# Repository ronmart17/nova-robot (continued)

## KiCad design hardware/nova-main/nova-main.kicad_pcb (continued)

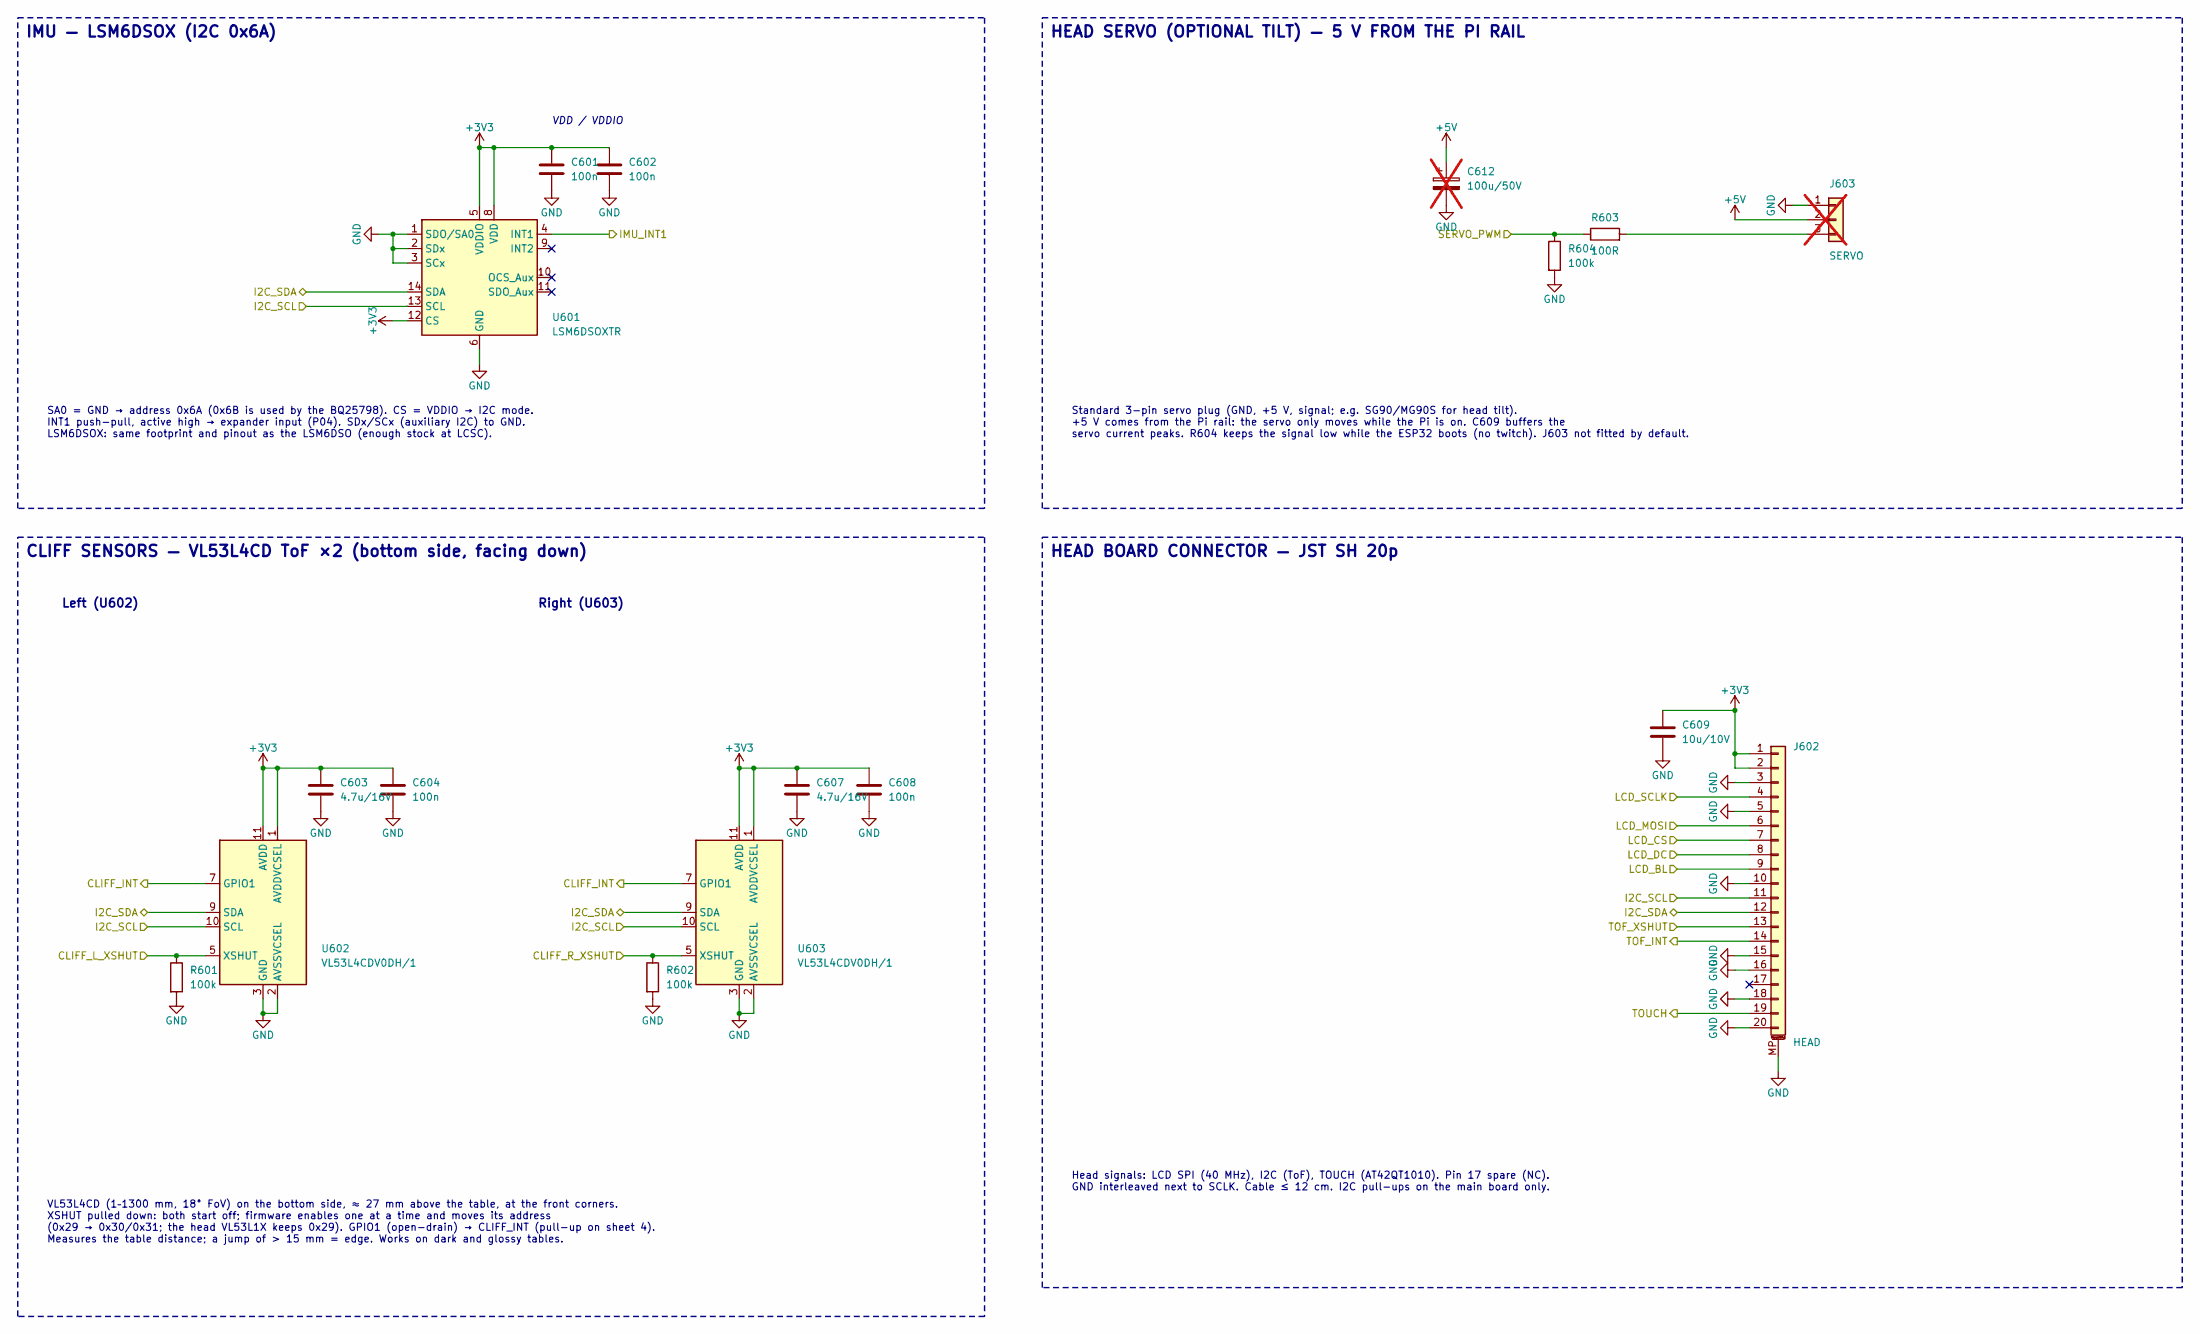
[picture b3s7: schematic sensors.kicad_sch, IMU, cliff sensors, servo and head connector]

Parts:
C601, C602, C604, C608: 100n; C_0402_1005Metric; Voltage 50V; MPN CL05B104KB54PNC; LCSC C307331
C603, C607: 4.7u/16V; C_0603_1608Metric; Voltage 16V; MPN CL10A475KO8NNNC; LCSC C19666
C609: 10u/10V; C_0603_1608Metric; Voltage 10V; MPN CC0603KRX5R6BB106; LCSC C326057
C612: 100u/50V; CP_Elec_6.3x7.7; Voltage 50V; MPN EEE-FTH101XAP; LCSC C165974; not fitted
J602: HEAD; JST_SH_SM20B-SRSS-TB_1x20-1MP_P1.00mm_Horizontal; MPN SM20B-SRSS-TB(LF)(SN); LCSC C160415
J603: SERVO; PinHeader_1x03_P2.54mm_Vertical; MPN 2.54-1*3P header; LCSC C49257; not fitted
R601, R602, R604: 100k; R_0402_1005Metric; Tolerance 1%; MPN RC0402FR-07100KL; LCSC C60491
R603: 100R; R_0402_1005Metric; Tolerance 1%; MPN RC0402FR-07100RL; LCSC C106232
U601: LSM6DSOXTR; LGA-14_3x2.5mm_P0.5mm_LayoutBorder3x4y; MPN LSM6DSOXTR; LCSC C481766
U602, U603: VL53L4CDV0DH/1; ST_VL53L4CD; MPN VL53L4CDV0DH/1; LCSC C3178291

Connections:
/CLIFF_INT: U602.7 (GPIO1), U603.7 (GPIO1); also elsewhere on the board
/CLIFF_L_XSHUT: R601.1, U602.5 (XSHUT); also elsewhere on the board
/CLIFF_R_XSHUT: R602.1, U603.5 (XSHUT); also elsewhere on the board
/I2C_SCL: J602.11, U601.13 (SCL), U602.10 (SCL), U603.10 (SCL); also elsewhere on the board
/I2C_SDA: J602.12, U601.14 (SDA), U602.9 (SDA), U603.9 (SDA); also elsewhere on the board
/IMU_INT1: U601.4 (INT1); also elsewhere on the board
/LCD_BL: J602.9; also elsewhere on the board
/LCD_CS: J602.7; also elsewhere on the board
/LCD_DC: J602.8; also elsewhere on the board
/LCD_MOSI: J602.6; also elsewhere on the board
/LCD_SCLK: J602.4; also elsewhere on the board
/SERVO_PWM: R603.1, R604.1; also elsewhere on the board
/TOF_INT: J602.14; also elsewhere on the board
/TOF_XSHUT: J602.13; also elsewhere on the board
/TOUCH: J602.19; also elsewhere on the board
unnamed: J603.3, R603.2

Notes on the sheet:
IMU — LSM6DSOX (I2C 0x6A)
CLIFF SENSORS — VL53L4CD ToF ×2 (bottom side, facing down)
HEAD SERVO (OPTIONAL TILT) — 5 V FROM THE PI RAIL
HEAD BOARD CONNECTOR — JST SH 20p
VDD / VDDIO
SA0 = GND → address 0x6A (0x6B is used by the BQ25798). CS = VDDIO → I2C mode. INT1 push-pull, active high → expander input (P04). SDx/SCx (auxiliary I2C) to GND. LSM6DSOX: same footprint and pinout as the LSM6DSO (enough stock at LCSC).
Left (U602)
Right (U603)
VL53L4CD (1–1300 mm, 18° FoV) on the bottom side, ≈ 27 mm above the table, at the front corners. XSHUT pulled down: both start off; firmware enables one at a time and moves its address (0x29 → 0x30/0x31; the head VL53L1X keeps 0x29). GPIO1 (open-drain) → CLIFF_INT (pull-up on sheet 4). Measures the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
Standard 3-pin servo plug (GND, +5 V, signal; e.g. SG90/MG90S for head tilt). +5 V comes from the Pi rail: the servo only moves while the Pi is on. C609 buffers the servo current peaks. R604 keeps the signal low while the ESP32 boots (no twitch). J603 not fitted by default.
Head signals: LCD SPI (40 MHz), I2C (ToF), TOUCH (AT42QT1010). Pin 17 spare (NC). GND interleaved next to SCLK. Cable ≤ 12 cm. I2C pull-ups on the main board only.

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
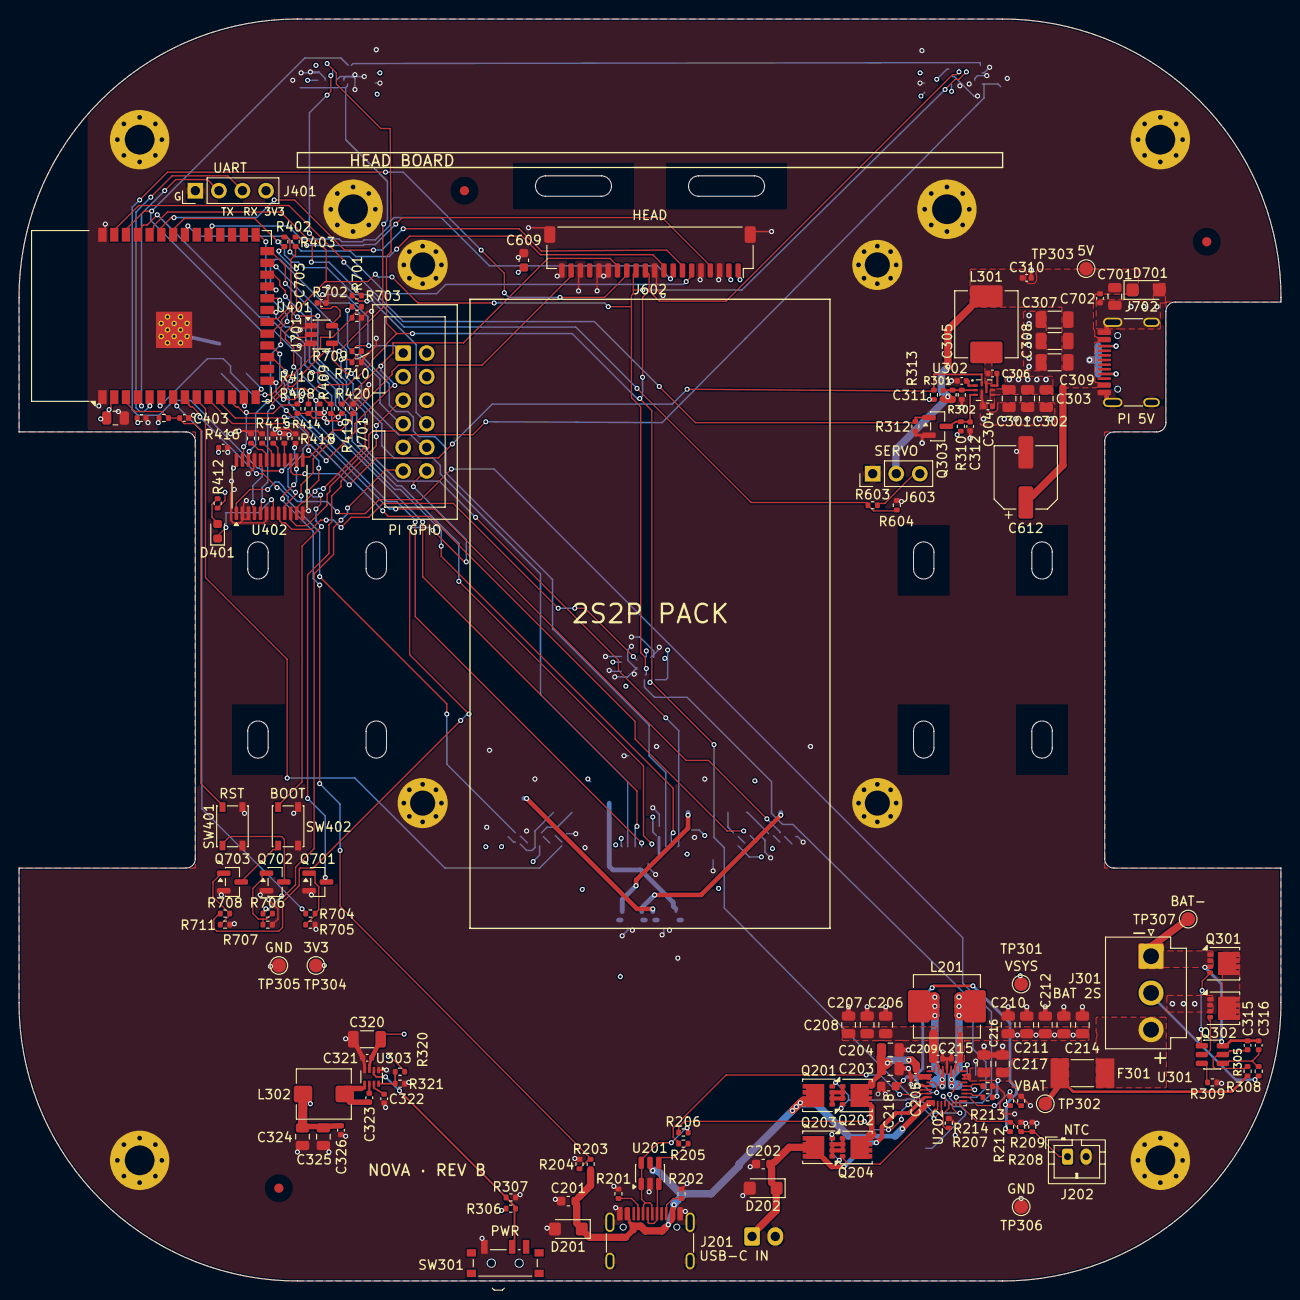
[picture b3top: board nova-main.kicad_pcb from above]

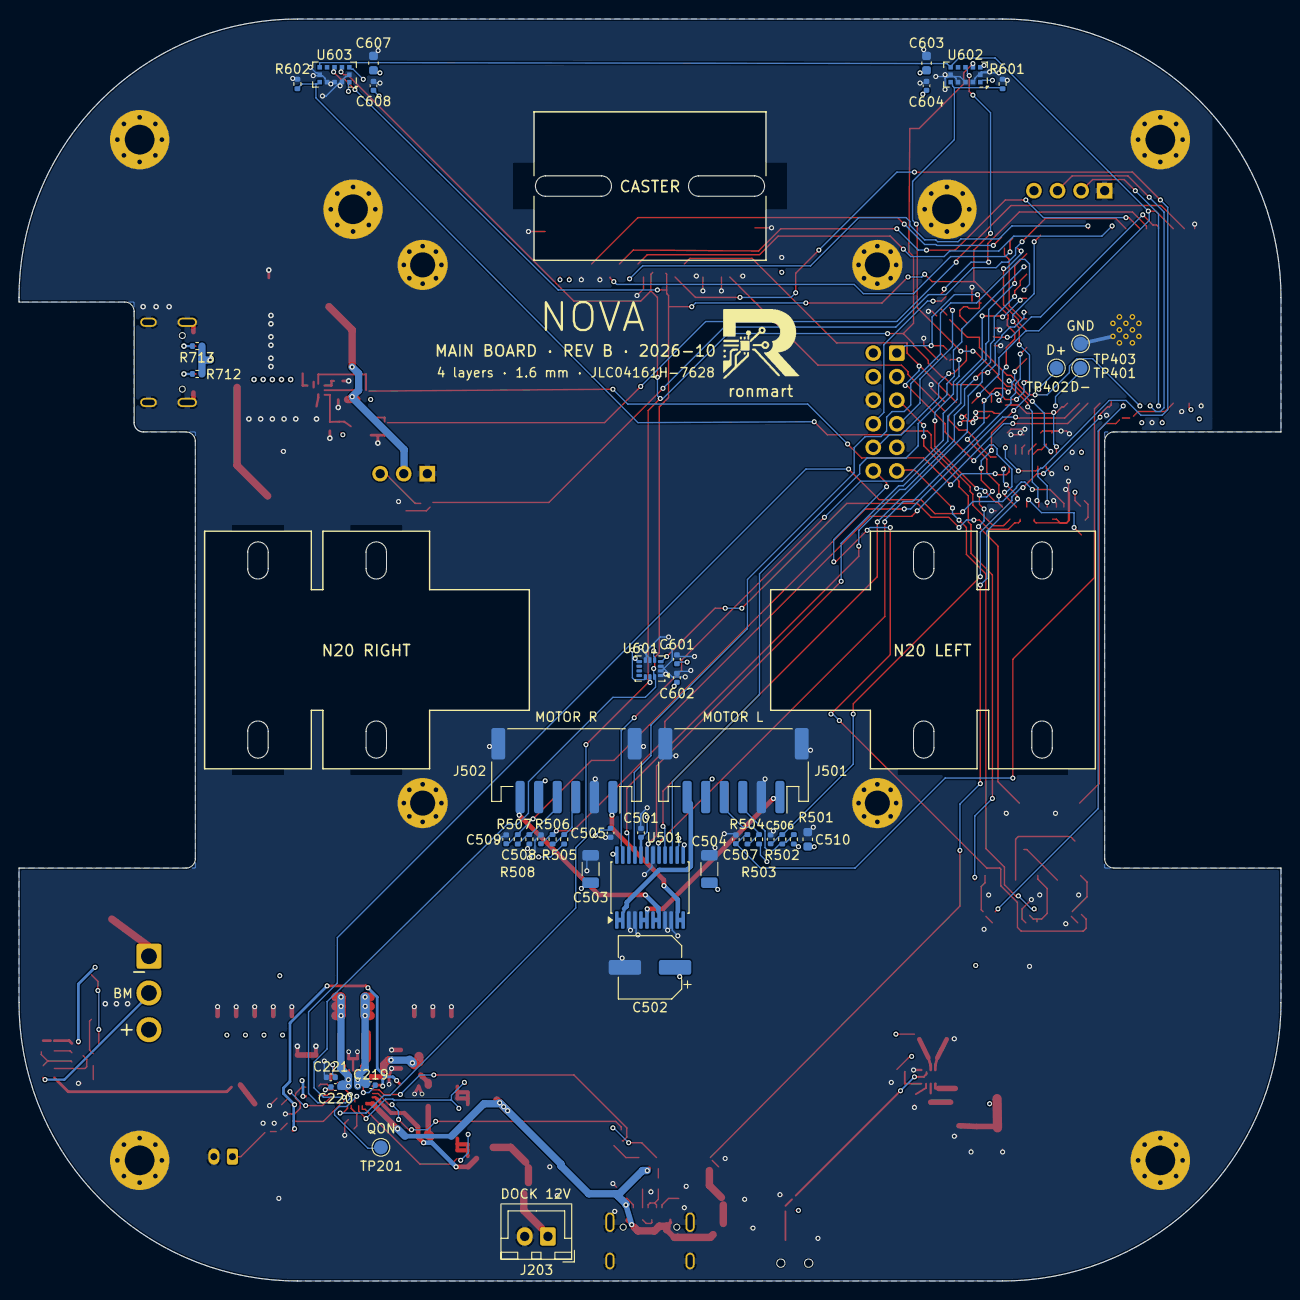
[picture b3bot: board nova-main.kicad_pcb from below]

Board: 4 copper layers, 136.0 x 136.0 mm, 201 parts (42 on the bottom side), 121 nets.

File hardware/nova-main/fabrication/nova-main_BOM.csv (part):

Item,Qty,Designators,Value,Footprint,Manufacturer,MPN,LCSC,Mouser,DigiKey,Alt MPN,Alt Mouser,Alt DigiKey,Description,Sourcing note,DNP
1,2,"C201, C202",1u/25V,C_0603_1608Metric,Yageo,CC0603KRX5R8BB105,C14664,603-CC603KRX5R8BB105,311-1445-1-ND,,,,MLCC 1uF 25V X5R 0603,,
2,15,"C203, C204, C206, C207, C208, C210, C211, C212, C213, C214, C216, C217, C301, C302, C303",10u/25V,C_0805_2012Metric,Samsung,CL21A106KAYNNNE,C15850,187-CL21A106KAYNNNE,1276-6455-1-ND,,,,MLCC 10uF 25V X5R 0805,JLC Basic,
3,21,"C205, C209, C215, C304, C306, C310, C315, C316, C321, C323, C326, C402, C404, C501, C505, C601, C602, C604, C608, C702, C703",100n,C_0402_1005Metric,Samsung,CL05B104KB54PNC,C307331,187-CL05B104KB54PNC,1276-CL05B104KB54PNCCT-ND,,,,MLCC 100nF 50V X7R 0402,JLC Basic,
4,3,"C218, C603, C607",4.7u/16V,C_0603_1608Metric,Samsung,CL10A475KO8NNNC,C19666,,1276-1784-1-ND,,,,MLCC 4.7uF 16V X5R 0603,JLC Basic,
5,2,"C219, C220",47n,C_0402_1005Metric,Samsung,CL05B473KA5NNNC,C318631,187-CL05B473KA5NNNC,,,,,MLCC 47nF 25V X7R 0402,,
6,6,"C221, C312, C506, C507, C508, C509",1n,C_0402_1005Metric,Samsung,CL05B102KB5NNNC,C14442,187-CL05B102KB5NNNC,1276-1032-1-ND,,,,MLCC 1nF 50V X7R 0402,,
7,2,"C305, C403",1u/25V,C_0402_1005Metric,Samsung,CL05A105KA5NQNC,C52923,187-CL05A105KA5NQNC,1276-1445-1-ND,,,,MLCC 1uF 25V X5R 0402,JLC Basic,
8,3,"C307, C308, C309",47u/10V,C_1206_3216Metric,Samsung,CL31A476MPHNNNE,C96123,,,,,,MLCC 47uF 10V X5R 1206,JLC Basic; alt. Murata GRM31CR61A476ME15L (C94034),
9,1,C311,33p C0G,C_0402_1005Metric,Samsung,CL05C330JB5NNNC,C70465,187-CL05C330JB5NNNC,1276-1009-1-ND,,,,MLCC 33pF 50V C0G 0402,,
10,3,"C320, C503, C504",22u/25V,C_1206_3216Metric,Samsung,CL31A226KAHNNNE,C12891,,1276-3047-6-ND,,,,MLCC 22uF 25V X5R 1206,JLC Basic; Western sourcing: Yageo CC1206MKX5R8BB226 (Mouser/DigiKey),
11,1,C322,33n,C_0402_1005Metric,Samsung,CL05B333KB5VPNC,C472437,187-CL05B333KB5VPNC,,,,,MLCC 33nF 50V X7R 0402,,
12,4,"C324, C325, C401, C701",22u/10V,C_0805_2012Metric,Taiyo Yuden,LMK212BJ226MG-T,C92814,963-LMK212BJ226MG-T,587-1958-1-ND,,,,MLCC 22uF 10V X5R 0805,,
13,1,C502,100u/50V,CP_Elec_6.3x7.7,Panasonic,EEE-FTH101XAP,C165974,667-EEE-FTH101XAP,PCE5024CT-ND,,,,"Aluminium electrolytic 100uF 50V, 6.3x7.7 mm, ESR 0.34 ohm — damping bulk on VM",,
14,2,"C510, C609",10u/10V,C_0603_1608Metric,Yageo,CC0603KRX5R6BB106,C326057,603-CC603KRX5R6BB106,,,,,MLCC 10uF 10V X5R 0603,JLC Basic alt C19702,
15,1,C612,100u/50V,CP_Elec_6.3x7.7,Panasonic,EEE-FTH101XAP,C165974,667-EEE-FTH101XAP,PCE5024CT-ND,,,,"Aluminium electrolytic 100uF 50V, 6.3x7.7 mm, ESR 0.34 ohm — damping bulk on VM",,DNP
16,1,D201,SMF12A,D_SMF,Littelfuse,SMF12A,C123800,576-SMF12A,,,,,"TVS unidirectional 12V standoff (VBR 13.3-14.7V, Vc 19.9V) 200W SMF — USB-C VBUS",,
17,1,D202,SMF15A,D_SMF,Littelfuse,SMF15A,C123802,576-SMF15A,,,,,"TVS unidirectional 15V standoff (VBR 16.7-18.5V, Vc 24.4V) 200W SMF — 12 V dock input",,
18,1,D401,Green,LED_0603_1608Metric,Lite-On,LTST-C191KGKT,C125098,859-LTST-C191KGKT,160-1446-1-ND,,,,LED yellow-green 574 nm 0603,,
19,1,D701,SMF6.0A,D_SMF,Littelfuse,SMF6.0A,C123790,576-SMF6.0A,,,,,"TVS unidirectional 6.0V standoff (VBR 6.67-7.37V, Vc 10.3V) 200W SMF — Pi 5 V rail",,
20,1,F301,10A very fast,Fuse_Littelfuse-NANO2-451_453,Littelfuse,0451010.MRL,C44479,576-0451010.MRL,F2350CT-ND,,,,"SMD fuse NANO2 10A very fast-acting, 125V, 5.6 mOhm, 2410 (6.1x2.69 mm)",,
21,2,"J201, J702",USB-C,USB_C_Receptacle_HRO_TYPE-C-31-M-12_GCT_USB4105,Korean Hroparts Elec,TYPE-C-31-M-12,C165948,,,USB4105-GF-A (GCT),640-USB4105-GF-A,2073-USB4105-GF-ACT-ND,"USB-C receptacle USB 2.0, 16P, top mount, horizontal (HRO TYPE-C-31-M-12 / GCT USB4105-GF-A)","Approved alternative on the same footprint: GCT USB4105-GF-A (Mouser 640-USB4105-GF-A, DigiKey 2073-USB4105-GF-ACT-ND)",
22,1,J202,NTC,JST_PH_B2B-PH-K_1x02_P2.00mm_Vertical,JST,B2B-PH-K-S(LF)(SN),C131337,306-B2BPHKSLFSN,455-1704-ND,,,,JST PH 2-pin — 10k NTC (103AT) taped to the cells,Vertical (top entry) since the PCB phase,
23,1,J203,DOCK 12V,JST_XH_B2B-XH-A_1x02_P2.50mm_Vertical,JST,B2B-XH-A(LF)(SN),C158012,306-B2B-XH-ALFSN,455-2247-ND,,,,"JST XH 2-pin vertical, 3 A — wires from the dock contact plate (1 = +12 V, 2 = GND)",,
24,1,J301,BATTERY 2S,JST_VH_B3P-VH_1x03_P3.96mm_Vertical,JST,B3P-VH(LF)(SN),C160316,306-B3P-VHLFSN,,,,,"JST VH 3-pin 3.96 mm, 10 A — 2S pack: 1 B-, 2 BM, 3 B+",,
25,1,J401,UART,PinHeader_1x04_P2.54mm_Vertical,Molex,22-28-4040,C587039,538-22-28-4040,,,,,Debug UART header 1x4 2.54 mm (not fitted),,DNP
26,2,"J501, J502",MOTOR+ENC,JST_PH_S6B-PH-SM4-TB_1x06-1MP_P2.00mm_Horizontal,JST,S6B-PH-SM4-TB(LF)(SN),C265405,,,,,,"JST PH 6-pin SMD side entry (bottom side, under the pack) — N20 motor with Hall encoder",,
27,1,J602,HEAD,JST_SH_SM20B-SRSS-TB_1x20-1MP_P1.00mm_Horizontal,JST,SM20B-SRSS-TB(LF)(SN),C160415,306-SM20BSRSSTBLFSN,455-SM20B-SRSS-TBCT-ND,,,,JST SH 20-pin SMD — cable to head board,,
28,1,J603,SERVO,PinHeader_1x03_P2.54mm_Vertical,BOOMELE,2.54-1*3P header,C49257,,,,,,"Pin header 1x3 2.54 mm — hobby servo (1 GND, 2 +5V, 3 signal)",Not fitted until a tilt servo is added,DNP
29,1,J701,PI GPIO 1-12,IDC-Header_2x06_P2.54mm_Vertical,BOOMELE,2.54-2*6P box header,C9136,,,,,,"Box header 2x6 2.54 mm, shrouded, vertical — IDC ribbon to Raspberry Pi 5 header pins 1-12",Any 2x6 2.54 mm shrouded box header fits,
30,2,"L201, L301",2.2uH,L_Sunlord_MWSA0605S,Sunlord,MWSA0605S-2R2MT,C408463,,,,,,"Power inductor 2.2uH 20%, Isat 11A, Irms 9A, 12.5 mOhm, shielded 7.0x6.6x5.0 mm","Alt. TAI-TECH TMPC0605H-2R2MG-D (C357209), same land pattern class",
31,1,L302,3.3uH,L_Bourns_SRP5030T,Bourns,SRP5030T-3R3M,C189931,652-SRP5030T-3R3M,SRP5030T-3R3MCT-ND,,,,"Power inductor 3.3uH 20%, Isat 8A, Irms 5A, 38 mOhm, shielded 5.7x5.2 — TPS62933 at 1.2 MHz",,
32,4,"Q201, Q202, Q203, Q204",CSD17578Q3A,VSON-8_3.3x3.3mm_P0.65mm_NexFET,Texas Instruments,CSD17578Q3A,C205986,595-CSD17578Q3A,,,,,"30V N-channel NexFET, 9.4 mOhm @ VGS 4.5V, VSON-8 3.3x3.3 mm",,
33,2,"Q301, Q302",CSD17579Q3A,VSON-8_3.3x3.3mm_P0.65mm_NexFET,Texas Instruments,CSD17579Q3A,C97376,595-CSD17579Q3A,,,,,"30V N-channel NexFET, 8.7 mOhm @ VGS 10V, VSON-8 3.3x3.3 mm",,
34,4,"Q303, Q701, Q702, Q703",2N7002LT1G,SOT-23,onsemi,2N7002LT1G,C16338,863-2N7002LT1G,2N7002LT1GOSCT-ND,,,,N-MOSFET 60V 115mA SOT-23,,
35,2,"R201, R202",5.1k,R_0402_1005Metric,Yageo,RC0402FR-075K1L,C105872,603-RC0402FR-075K1L,311-5.10KLRCT-ND,,,,Thick-film resistor 5.1k 1% 0402,JLC Basic alt C25905,
36,13,"R203, R214, R310, R312, R420, R601, R602, R604, R703, R705, R707, R710, R711",100k,R_0402_1005Metric,Yageo,RC0402FR-07100KL,C60491,603-RC0402FR-07100KL,311-100KLRCT-ND,,,,Thick-film resistor 100k 1% 0402,JLC Basic alt C25741,
37,1,R204,200k,R_0402_1005Metric,Yageo,RC0402FR-07200KL,C114763,603-RC0402FR-07200KL,311-200KLRCT-ND,,,,Thick-film resistor 200k 1% 0402,JLC Basic alt C25764,
38,2,"R205, R206",0R,R_0402_1005Metric,Yageo,RC0402JR-070RL,C60485,603-RC0402JR-070RL,311-0.0JRCT-ND,,,,Thick-film resistor 0R 1% 0402,JLC Basic alt C17168,
39,1,R207,5.23k,R_0402_1005Metric,Vishay,CRCW04025K23FKED,C2076550,71-CRCW0402-5.23K-E3,541-5.23KLCT-ND,,,,Thick-film resistor 5.23k 1% 0402,,
40,1,R208,30.1k,R_0402_1005Metric,Panasonic,ERJ-2RKF3012X,C2076806,667-ERJ-2RKF3012X,P30.1KLCT-ND,,,,Thick-film resistor 30.1k 1% 0402,,
41,1,R209,10k,R_0402_1005Metric,Yageo,RC0402FR-0710KL,C60490,603-RC0402FR-0710KL,311-10.0KLRCT-ND,,,,Thick-film resistor 10k 1% 0402,,DNP
42,1,R210,4.7k,R_0402_1005Metric,Yageo,RC0402FR-074K7L,C105871,603-RC0402FR-074K7L,,,,,Thick-film resistor 4.7k 1% 0402,JLC Basic alt C25900,
43,19,"R212, R313, R321, R401, R410, R411, R414, R415, R416, R417, R418, R419, R501, R503, R505, R507, R709, R712, R713",10k,R_0402_1005Metric,Yageo,RC0402FR-0710KL,C60490,603-RC0402FR-0710KL,311-10.0KLRCT-ND,,,,Thick-film resistor 10k 1% 0402,,
44,1,R213,8.2k,R_0402_1005Metric,UNI-ROYAL,0402WGF8201TCE,C25924,,,,,,Thick-film resistor 8.2k 1% 0402,JLC Basic,
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
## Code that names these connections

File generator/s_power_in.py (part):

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    src = f'{acdrv}_S'
    sh.wire((asx, asy), (bsx, bsy)); sh.assign(a, 'S', src); sh.assign(b, 'S', src)
    sh.wire((adx, ady), (adx - 15.24, ady)); sh.label(vin, (adx - 15.24, ady), (-1, 0)); sh.assign(a, 'D', vin)
    sh.wire((bdx, bdy), (bdx + 15.24, bdy)); sh.label('CHG_VBUS', (bdx + 15.24, bdy), (1, 0)); sh.assign(b, 'D', 'CHG_VBUS')
    yg = agy + 5.08
    sh.wire((agx, agy), (agx, yg)); sh.wire((bgx, bgy), (bgx, yg)); sh.wire((agx, yg), (bgx, yg))
    xm = (agx + bgx) / 2
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
    # ------------------------------------------------------------------ USB-C
    j = place_part(sh, 'J_USBC', 'J201', 43.18, 76.2, ref_at=(-10.16, -20.955, 'left'), val_at=(-10.16, -18.415, 'left'))
    (vx, vy), _ = j.pin('A4'); sh.assign(j, 'A4', 'VBUS_USB')
    sh.wire((vx, vy), (vx + 12.7, vy)); sh.label('VBUS_USB', (vx + 12.7, vy), (1, 0))
    for pin, net in (('A5', 'CC1'), ('B5', 'CC2')):
        sh.pin_label(j, pin, net, length=12.7)
    for (pa, pb, net, xj) in (('A7', 'B7', 'USB_DM', 60.96), ('A6', 'B6', 'USB_DP', 63.5)):
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    # ESD on D+/D- (and VBUS)
    e = place_part(sh, 'U_USBLC6', 'U201', 101.6, 104.14, ref_at=(5.08, -6.35, 'left'), val_at=(5.08, -3.81, 'left'))
    (p1x, p1y), _ = e.pin('1'); (p3x, p3y), _ = e.pin('3')
    sh.wire((p1x, p1y), (p1x - 10.16, p1y)); sh.label('USB_DM', (p1x - 10.16, p1y), (-1, 0)); sh.assign(e, '1', 'USB_DM')
    sh.wire((p3x, p3y), (p3x - 10.16, p3y)); sh.label('USB_DP', (p3x - 10.16, p3y), (-1, 0)); sh.assign(e, '3', 'USB_DP')
    sh.pin_label(e, '6', 'USB_DM', length=12.7)          # D+/D− of the USB-C input: BC1.2 detection only (R205/R206)
    sh.pin_label(e, '4', 'USB_DP', length=12.7)
    sh.pin_label(e, '5', 'VBUS_USB', length=5.08)
    sh.pin_power(e, '2', 'GND', length=2.54)
    # VBUS TVS + local capacitor
    tv = place_vertical_k_top(sh, 'D_TVS_12V', 'D201', 30.48, 116.84, fpos='right')
    (k1, _), (a1, _) = tv.pin('1'), tv.pin('2')
    sh.assign(tv, '1', 'VBUS_USB'); sh.assign(tv, '2', 'GND')
    sh.wire(k1, (k1[0], k1[1] - 5.08)); sh.label('VBUS_USB', (k1[0], k1[1] - 5.08), (0, -1)); sh.power('GND', a1)
    vpart_between(sh, 'C_1u_25V', 'C201', 53.34, 109.22, ('label', 'VBUS_USB', 2.54), 'GND')
    # VBUS detection for the ESP32 USB device (→ expander P11)
    r3 = vpart_between(sh, 'R_100k', 'R203', 66.04, 106.68, ('label', 'VBUS_USB', 2.54), None)
    r4 = vpart_between(sh, 'R_200k', 'R204', 66.04, 114.3, None, 'GND')
    sh.assign(r3, '2', 'VBUS_DET'); sh.assign(r4, '1', 'VBUS_DET')
    sh.wire((66.04, 114.3), (78.74, 114.3)); sh.hlabel('VBUS_DET', (78.74, 114.3), (1, 0), 'output')
    sh.text('VBUS_DET: 5 V → 3.33 V', (63.5, 133.35), size=1.27, italic=True)
    sh.text('D201 SMF12A + C201\nat the connector', (25.4, 133.35), size=1.27, italic=True)

    # ------------------------------------------------------------------ dock input
    jd = place_part(sh, 'J_DOCK', 'J203', 35.56, 165.1, mirror='y', ref_at=(-6.35, -5.08, 'left'), val_at=(-6.35, 7.62, 'left'))
    (d1x, d1y), _ = jd.pin('1'); (d2x, d2y), _ = jd.pin('2')
    sh.wire((d1x, d1y), (114.3, d1y)); sh.assign(jd, '1', 'VDOCK'); sh.label('VDOCK', (114.3, d1y), (1, 0))
    sh.wire((d2x, d2y), (d2x + 5.08, d2y)); sh.wire((d2x + 5.08, d2y), (d2x + 5.08, d2y + 7.62)); sh.power('GND', (d2x + 5.08, d2y + 7.62))
    sh.assign(jd, '2', 'GND')
    td = place_vertical_k_top(sh, 'D_TVS_15V', 'D202', 71.12, d1y + 7.62, fpos='right')
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    sh.power('PWR_FLAG', (101.6, d1y))
    sh.text('J203 (bottom side): wires from the dock contact plate.\n1 = +12 V, 2 = GND. D202 SMF15A clamps hot-plug\nringing below the 30 V abs. max of VAC2.',
            (25.4, 182.88), size=1.27)
    sh.power('PWR_FLAG', (121.92, 60.96)); sh.wire((121.92, 60.96), (121.92, 66.04)); sh.label('VBUS_USB', (121.92, 66.04), (0, 1))

    # ------------------------------------------------------------------ input selector
    fet_pair(sh, 175.26, 60.96, 'Q201', 'Q202', 'VBUS_USB', 'ACDRV1', 'PAIR 1 — USB-C (VAC1, BC1.2 detection)')
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         'D+': 'CHG_DP', '~{QON}': 'CHG_QON', 'ILIM_HIZ': 'CHG_ILIM', 'PROG': 'CHG_PROG', 'TS': 'CHG_TS'}
    for pin, net in L.items():
        sh.pin_label(u, pin, net, length=7.62)
    for pin, net, shape in (('SCL', 'I2C_SCL', 'input'), ('SDA', 'I2C_SDA', 'bidirectional'), ('~{INT}', 'IRQ_N', 'output')):
        (px, py), _ = u.pin(pin)
        sh.wire((px, py), (px - 20.32, py)); sh.assign(u, pin, net); sh.hlabel(net, (px - 20.32, py), (-1, 0), shape)
    # ~CE held low by R214: charging enabled in hardware; firmware switches charging with EN_CHG (REG0x0F) over I2C
    (px, py), _ = u.pin('~{CE}')
    sh.wire((px, py), (px - 20.32, py)); sh.assign(u, '~{CE}', 'CHG_CE'); sh.label('CHG_CE', (px - 20.32, py), (-1, 0))
    R = {'PMID': 'CHG_PMID', 'BTST1': 'CHG_BTST1', 'SW1': 'CHG_SW1', 'SW2': 'CHG_SW2', 'BTST2': 'CHG_BTST2',
         'REGN': 'CHG_REGN', 'SDRV': 'CHG_SDRV', 'BATP': 'CHG_BATP'}
    for pin, net in R.items():
        sh.pin_label(u, pin, net, length=7.62)
    for pin, net, dx in (('SYS', 'VSYS', 12.7), ('BAT', 'VBAT', 22.86)):
        (px, py), _ = u.pin(pin); sh.assign(u, pin, net)
        sh.wire((px, py), (px + dx, py)); sh.power(net, (px + dx, py))
    sh.pin_power(u, 'GND', 'GND', length=2.54)
    sh.power('PWR_FLAG', (285.75, 63.5)); sh.wire((285.75, 63.5), (285.75, 68.58)); sh.label('CHG_VBUS', (285.75, 68.58), (0, 1))
    sh.text('U202 pins 2/3 (VBUS) and 22/23 (BAT) are\ndoubled in the package.', (264.16, 142.24), size=1.27, italic=True)

    # inductor and bootstraps
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    (la, _), (lb, _) = l.pin('1'), l.pin('2')
    lp, rp = ('1', '2') if la[0] < lb[0] else ('2', '1')
    (lx, ly), _ = l.pin(lp); (rx, ry), _ = l.pin(rp)
    sh.wire((lx, ly), (lx - 7.62, ly)); sh.label('CHG_SW1', (lx - 7.62, ly), (-1, 0)); sh.assign(l, lp, 'CHG_SW1')
    sh.wire((rx, ry), (rx + 7.62, ry)); sh.label('CHG_SW2', (rx + 7.62, ry), (1, 0)); sh.assign(l, rp, 'CHG_SW2')
    vpart_between(sh, 'C_47n', 'C219', 312.42, 157.48, ('label', 'CHG_BTST1', 2.54), ('label', 'CHG_SW1', 2.54))
    vpart_between(sh, 'C_47n', 'C220', 327.66, 157.48, ('label', 'CHG_BTST2', 2.54), ('label', 'CHG_SW2', 2.54))
    vpart_between(sh, 'C_4u7', 'C218', 342.9, 157.48, ('label', 'CHG_REGN', 2.54), 'GND')
    vpart_between(sh, 'C_1n', 'C221', 358.14, 157.48, ('label', 'CHG_SDRV', 2.54), 'GND')
    rb = vpart_between(sh, 'R_100', 'R215', 373.38, 157.48, ('label', 'CHG_BATP', 2.54), None)
    (bx2, by2), _ = rb.pin('2'); sh.assign(rb, '2', 'VBAT'); sh.wire((bx2, by2), (bx2, by2 + 2.54)); sh.power('VBAT', (bx2, by2 + 2.54), rot=180)
    sh.text('L201 2.2 µH (Isat 11 A) between SW1 and SW2: one inductor for buck and boost.\n'
            'C219/C220 47 nF bootstraps. C218 REGN. C221: SDRV with no ship FET.\nR215: BATP sense, 100 Ω to the pack.',
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    # configuration network
    sh.text('CONFIGURATION, TS (NTC), STATUS', (264.16, 195.58), size=1.524, bold=True)
    yr = 208.28
    r = vpart_between(sh, 'R_4k7', 'R210', 269.24, yr, ('label', 'CHG_REGN', 2.54), None)
    r2 = vpart_between(sh, 'R_10k', 'R212', 269.24, yr + 10.16, None, 'GND')
    sh.connect('CHG_ILIM', (r, '2'), (r2, '1'))
    sh.wire((269.24, yr + 10.16), (276.86, yr + 10.16)); sh.label('CHG_ILIM', (276.86, yr + 10.16), (1, 0))
    vpart_between(sh, 'R_8k2', 'R213', 292.1, yr, ('label', 'CHG_PROG', 2.54), 'GND')
    rt1 = vpart_between(sh, 'R_5k23', 'R207', 307.34, yr, ('label', 'CHG_REGN', 2.54), None)
    rt2 = vpart_between(sh, 'R_30k1', 'R208', 307.34, yr + 10.16, None, 'GND')
    sh.connect('CHG_TS', (rt1, '2'), (rt2, '1'))
    sh.wire((307.34, yr + 10.16), (325.12, yr + 10.16)); sh.label('CHG_TS', (314.96, yr + 10.16), (1, 0))
    vpart_between(sh, 'R_10k', 'R209', 325.12, yr + 10.16, ('net', 'CHG_TS'), 'GND', dnp=True)
    jn = place_part(sh, 'J_NTC', 'J202', 345.44, yr + 10.16, ref_at=(-1.27, -3.81, 'left'), val_at=(-1.27, 6.35, 'left'))
    (n1x, n1y), _ = jn.pin('1'); (n2x, n2y), _ = jn.pin('2')
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    # STAT (open drain) not used: the charge LED would be hidden inside the enclosure; the charge state is read over
    # I2C and shown on the face display. Firmware sets DIS_STAT = 1.
    sh.pin_nc(u, 'STAT')
    rc = vpart_between(sh, 'R_100k', 'R214', 373.38, yr, ('label', 'CHG_CE', 2.54), 'GND')
    t = place_part(sh, 'TP', 'TP201', 388.62, yr + 2.54, ref_at=(1.27, -5.715, 'left'), hide_value=True, val_at=(1.27, -3.175, 'left'))
    (tx, ty), _ = t.pin('1'); sh.assign(t, '1', 'CHG_QON'); sh.wire((tx, ty), (tx, ty + 5.08)); sh.label('CHG_QON', (tx, ty + 5.08), (0, 1))
    for i, (ref, a, b) in enumerate((('R205', 'CHG_DP', 'USB_DP'), ('R206', 'CHG_DM', 'USB_DM'))):
        yy = 233.68 + i * 7.62
        rr = place_part(sh, 'R_0', ref, 279.4, yy, rot=90)
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
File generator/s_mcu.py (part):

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    # ------------------------------------------------------------------ reset and boot
    sh.text('RESET AND BOOT', (25.4, 152.4), size=1.524, bold=True)
    y = 167.64
    sh.hlabel('ESP_EN', (33.02, y), (-1, 0), 'bidirectional'); sh.wire((33.02, y), (71.12, y))
    vpart_between(sh, 'R_10k', 'R401', 40.64, y - 7.62, '+3V3', ('net', 'ESP_EN'))
    vpart_between(sh, 'C_1u', 'C403', 55.88, y, ('net', 'ESP_EN'), 'GND')
    sw = place_part(sh, 'SW_PUSH', 'SW401', 71.12, y + 5.08, rot=270, ref_at=(3.81, -1.27, 'left'), val_at=(3.81, 1.27, 'left'))
    (s1x, s1y), _ = sw.pin('1'); (s2x, s2y), _ = sw.pin('2')
    top, bot = ('1', '2') if s1y < s2y else ('2', '1')
    sh.assign(sw, top, 'ESP_EN'); sh.pin_power(sw, bot, 'GND', length=0)
    sh.text('RESET', (74.93, y + 10.16), size=1.27, italic=True)
    xb = 91.44
    sh.hlabel('ESP_BOOT', (xb, y), (-1, 0), 'bidirectional'); sh.wire((xb, y), (106.68, y))
    sw2 = place_part(sh, 'SW_PUSH', 'SW402', 106.68, y + 5.08, rot=270, ref_at=(3.81, -1.27, 'left'), val_at=(3.81, 1.27, 'left'))
    (s1x, s1y), _ = sw2.pin('1'); (s2x, s2y), _ = sw2.pin('2')
    top, bot = ('1', '2') if s1y < s2y else ('2', '1')
    sh.assign(sw2, top, 'ESP_BOOT'); sh.pin_power(sw2, bot, 'GND', length=0)
    sh.text('BOOT (GPIO0)', (110.49, y + 10.16), size=1.27, italic=True)
    sh.text('EN: RC 10 kΩ / 1 µF (τ = 10 ms): the ESP32 starts\nonce 3V3 is already stable.\n'
            'GPIO0 has internal pull-up: BOOT + RESET = download.\nDevelopment: native USB (GPIO19/20) on test pads TP401–TP403;\nthe Pi can also reset/boot the ESP32 (sheet 7) and flash it over UART0\n(ROM bootloader, esptool on /dev/serial0).',
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        sh.assign(r, right_pin, net); sh.hlabel(net, (hx, ay), (1, 0), shape)

    notes = ('NOTES\n'
             '• Strapping: GPIO45 (VDD_SPI) only drives MOT_STBY with pull-down → 3.3 V flash. GPIO46: test point only (internal pull-down).\n'
             '• GPIO3 → IRQ_N (JTAG on GPIO3 only if the eFuse is burned). GPIO35–37: octal PSRAM, do not use.\n'
             '• GPIO1 (RTC GPIO, held in deep sleep) → PI_PWR_OFF (high = Pi rail off). UART0 (GPIO43/44) = link to the Pi (also ROM download);\n  GPIO4/5 = UART1 on the debug header J401. GPIO41 → servo PWM. Pin map chosen for the board layout (rear signals on the right column).\n'
             '• GPIO19/20: native USB on test pads only (short stubs). 33 Ω series on the display SPI: limits edge rates into the head cable.\n'
             '• Antenna at the left board edge: keep-out (no copper, all layers) under and around the antenna.')
    sh.text(notes, (25.4, 223.52), size=1.27)
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    # ------------------------------------------------------------------ expander
    ex, ey = 309.88, 83.82
    e = place_part(sh, 'U_TCA9535', 'U402', ex, ey, ref_at=(-12.7, -24.765, 'left'), val_at=(1.27, 24.765, 'left'))
    for pin, net, shape in (('SDA', 'I2C_SDA', 'bidirectional'), ('SCL', 'I2C_SCL', 'input'), ('~{INT}', 'IRQ_N', 'output')):
        (px, py), _ = e.pin(pin)
        sh.wire((px, py), (271.78, py)); sh.assign(e, pin, net); sh.hlabel(net, (271.78, py), (-1, 0), shape)
    xa = 284.48
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    for pin, (net, shape) in ports.items():
        sh.pin_label(e, pin, net, length=17.78, kind='hier', shape=shape)
    sh.pin_power(e, 'P02', 'GND', length=7.62)             # spare input, tied low (configure as input only)
    sh.pin_label(e, 'P03', 'LED_STAT', length=48.26)
    sh.pin_label(e, 'P11', 'VBUS_DET', length=17.78, kind='hier', shape='input')
    sh.pin_label(e, 'P12', 'PI_5V_PG', length=17.78, kind='hier', shape='input')
    # P13–P17 unused: 10 kΩ to GND (TI: do not leave inputs floating); staircase fan-out without crossings
    pulls = [('P13', 'R414'), ('P14', 'R415'), ('P15', 'R416'), ('P16', 'R417'), ('P17', 'R418')]
    cols = [345.44 + i * 10.16 for i in range(5)]
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        sh.wire((bx, by), (bx, by + 7.62))
        sh.hlabel(net, (bx, by + 7.62), (0, 1), shape)
    sh.text('I2C pull-ups 2.2 kΩ: 400 kHz with ~150 pF\n(BQ25798, TCA9535, LSM6DSOX, 3× VL53Lx and cable).\n'
            'IRQ_N: BQ25798 and TCA9535 INT outputs, open-drain, wired-OR.\nCLIFF_INT: both VL53L4CD GPIO1 (open-drain), wired-OR.', (226.06, 203.2), size=1.27)
    rt = vpart_between(sh, 'R_100k', 'R420', 297.18, 170.18, None, 'GND')
    (tx, ty), _ = rt.pin('1'); sh.assign(rt, '1', 'TOUCH'); sh.wire((tx, ty), (tx, ty - 2.54)); sh.hlabel('TOUCH', (tx, ty - 2.54), (0, -1), 'input')
    rl = vpart_between(sh, 'R_1k', 'R412', 309.88, 162.56, '+3V3', None)
    d = place_part(sh, 'LED_G', 'D401', 309.88, 180.34, rot=90)
    sh.connect('LED_STAT_A', (rl, '2'), (d, '2'))
    sh.pin_label(d, '1', 'LED_STAT', length=5.08)
    sh.text('Status LED: active low,\ndriven from expander P03', (299.72, 203.2), size=1.27)
    j = place_part(sh, 'J_DBG', 'J401', 375.92, 175.26, mirror='x', dnp=True, ref_at=(-1.27, -8.89, 'left'), val_at=(-1.27, 8.89, 'left'))
    for pin, kind, dy in (('4', '+3V3', -5.08), ('1', 'GND', 5.08)):
        (px, py), _ = j.pin(pin)
        sh.wire((px, py), (px - 5.08, py)); sh.wire((px - 5.08, py), (px - 5.08, py + dy))
        sh.power(kind, (px - 5.08, py + dy)); sh.assign(j, pin, kind)
    sh.pin_label(j, '2', 'UART_TX', length=10.16)
    sh.pin_label(j, '3', 'UART_RX', length=10.16)
    sh.text('Debug UART1 (GPIO4/5, not fitted).\nTX/RX as seen from the ESP32.', (345.44, 203.2), size=1.27)

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
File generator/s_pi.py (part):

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from helpers import place_part, vpart_between, cap_rail, place_vertical_k_top

# Pi header pins 1-12 as seen on the 2x6 box header (straight IDC ribbon: pin n <-> pin n)
PI_PINS = {1: 'PI_3V3', 2: None, 3: None, 4: None, 5: 'PI_SHDN_N', 6: 'GND', 7: 'PI_GPIO4', 8: 'PI_TXD',
           9: 'GND', 10: 'PI_RXD', 11: 'PI_GPIO17', 12: 'PI_GPIO18'}

def hfet(sh, ref, rg, rpd, x, y, gate_net, drain_net, src_label, src_shape='input'):
    """2N7002 with series gate resistor and gate pull-down. (x, y) = transistor anchor.
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
    # ------------------------------------------------------------------ PI_3V3 -> PI_ON (expander)
    sh.text('PI ALIVE (Pi 3.3 V rail)', (25.4, 38.1), size=1.524, bold=True)
    r = vpart_between(sh, 'R_10k', 'R709', 50.8, 55.88, ('label', 'PI_3V3', 2.54), None)
    r2 = vpart_between(sh, 'R_100k', 'R710', 50.8, 68.58, None, 'GND')
    sh.connect('PI_ON', (r, '2'), (r2, '1'))
    sh.wire((50.8, 66.04), (66.04, 66.04)); sh.hlabel('PI_ON', (66.04, 66.04), (1, 0), 'output')
    sh.text('PI_ON = 1 while the Pi 3.3 V rail is up\n(→ expander P07). 100k keeps it at 0 V when off.', (25.4, 86.36), size=1.27)
    sh.power('PWR_FLAG', (81.28, 50.8)); sh.wire((81.28, 50.8), (81.28, 55.88)); sh.label('PI_3V3', (81.28, 55.88), (0, 1))
    sh.text('PI_3V3 comes from the Pi (J701 pin 1)', (73.66, 45.72), size=1.27, italic=True)

    # ------------------------------------------------------------------ UART: Pi TXD -> ESP32 RX (1k), ESP32 TX -> buffer -> Pi RXD
    sh.text('UART (ESP32 UART0 ↔ Pi UART0, GPIO14/15)', (25.4, 132.08), size=1.524, bold=True)
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    (a, _), (b, _) = rt.pin('1'), rt.pin('2')
    lp, rp = ('1', '2') if a[0] < b[0] else ('2', '1')
    (lx, ly), _ = rt.pin(lp); (rx, ry), _ = rt.pin(rp)
    sh.wire((lx, ly), (lx - 7.62, ly)); sh.label('PI_TXD', (lx - 7.62, ly), (-1, 0)); sh.assign(rt, lp, 'PI_TXD')
    sh.wire((rx, ry), (rx + 10.16, ry)); sh.hlabel('UART_PI_RX', (rx + 10.16, ry), (1, 0), 'output'); sh.assign(rt, rp, 'UART_PI_RX')
    sh.text('1 kΩ: limits current if only one side is powered', (25.4, 152.4), size=1.27, italic=True)
    u = place_part(sh, 'U_LVC1G125', 'U701', 63.5, 182.88, ref_at=(5.08, -10.16, 'left'), val_at=(5.08, -7.62, 'left'))
    (ax, ay), _ = u.pin('2'); sh.assign(u, '2', 'UART_PI_TX')
    sh.wire((ax, ay), (ax - 10.16, ay)); sh.hlabel('UART_PI_TX', (ax - 10.16, ay), (-1, 0), 'input')
    sh.pin_label(u, '4', 'PI_RXD', length=10.16)
    (ox, oy), _ = u.pin('1'); sh.assign(u, '1', 'GND')
    sh.wire((ox, oy), (ox, oy - 5.08)); sh.power('GND', (ox, oy - 5.08), rot=180)
    (vx, vy), _ = u.pin('5'); sh.assign(u, '5', 'PI_3V3')
    sh.wire((vx, vy), (vx, vy - 7.62)); sh.wire((vx, vy - 7.62), (vx - 15.24, vy - 7.62)); sh.label('PI_3V3', (vx - 15.24, vy - 7.62), (-1, 0))
    vpart_between(sh, 'C_100n', 'C703', vx - 7.62, vy - 7.62, ('net', 'PI_3V3'), 'GND')
    sh.pin_power(u, '3', 'GND', length=2.54)
    sh.text('U701 runs from the Pi 3.3 V rail: with the Pi off its\noutput is high-Z (Ioff), so the ESP32 TX cannot back-power\nthe Pi through GPIO15. OE tied low = always enabled.',
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    (a, _), (b, _) = rp4.pin('1'), rp4.pin('2')
    lp, rpn = ('1', '2') if a[0] < b[0] else ('2', '1')
    (lx, ly), _ = rp4.pin(lp); (rx, ry), _ = rp4.pin(rpn)
    sh.wire((lx, ly), (lx - 7.62, ly)); sh.label('PI_GPIO4', (lx - 7.62, ly), (-1, 0)); sh.assign(rp4, lp, 'PI_GPIO4')
    sh.wire((rx, ry), (rx + 15.24, ry)); sh.hlabel('PI_PWROFF', (rx + 15.24, ry), (1, 0), 'output'); sh.assign(rp4, rpn, 'PI_PWROFF')
    vpart_between(sh, 'R_100k', 'R703', rx + 7.62, ry, ('net', 'PI_PWROFF'), 'GND')
    # shutdown request: ESP32 -> Q701 -> Pi GPIO3 (open drain, 1.8k pull-up on the Pi)
    hfet(sh, 'Q701', 'R704', 'R705', 205.74, 187.96, 'PI_SHDN_REQ', ('PI_SHDN_N', 'local'), 'hier', 'input')
    # remote reset / boot of the ESP32 from the Pi (firmware update over UART)
    hfet(sh, 'Q702', 'R706', 'R707', 132.08, 187.96, 'PI_GPIO17', ('ESP_EN', 'hier'), 'local')
    hfet(sh, 'Q703', 'R708', 'R711', 132.08, 228.6, 'PI_GPIO18', ('ESP_BOOT', 'hier'), 'local')
    sh.text('Q701: ESP32 → GPIO3 low = shutdown request\n(dtoverlay=gpio-shutdown, default GPIO3).', (162.56, 210.82), size=1.27)
    sh.text('Q702/Q703: Pi GPIO17/18 hold ESP32 EN / GPIO0\nlow → the Pi can flash the ESP32 over UART.\nGPIO17/18 default to pull-down: no effect at boot.',
            (162.56, 228.6), size=1.27)
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             '• gpio-poweroff on the Pi 5 pulses (active 100 ms, inactive\n'
             '  100 ms, active): the ESP32 latches the FIRST rising edge.\n'
             '• Power sequence: ESP32 sends SHUTDOWN over UART (or pulls\n'
             '  GPIO3 low through Q701), waits for PI_PWROFF, waits 300 ms\n'
             '  and then switches the 5 V buck off (PI_PWR_OFF, sheet 3).')
    sh.text(notes, (254.0, 152.4), size=1.27)

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
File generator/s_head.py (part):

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        sh.pin_power(lcd, '1', 'GND', length=2.54)
        (q2x, q2y), _ = lcd.pin('2'); sh.assign(lcd, '2', '+3V3')
        sh.wire((q2x, q2y), (q2x - 10.16, q2y)); sh.wire((q2x - 10.16, q2y), (q2x - 10.16, q2y - 10.16)); sh.power('+3V3', (q2x - 10.16, q2y - 10.16))
        for pin, net in (('3', 'LCD_SCLK'), ('4', 'LCD_MOSI'), ('5', 'LCD_RES'), ('6', 'LCD_DC'), ('7', 'LCD_CS'), ('8', 'BL_OUT')):
            sh.pin_label(lcd, pin, net, length=15.24)
    sh.text('Module pin order: GND VCC SCL SDA RES DC CS BLK.\nJ102 (right) or J103 (left, DNP): fit only one,\nmatching the module orientation; pin 1 = GND on top.', (271.78, 99.06), size=1.27, italic=True)
    # reset RC
    rr = vpart_between(sh, 'R_10k', 'R101', 309.88, 45.72, '+3V3', None)
    cr = vpart_between(sh, 'C_100n', 'C103', 309.88, 58.42, None, 'GND')
    sh.connect('LCD_RES', (rr, '2'), (cr, '1'))
    sh.wire((309.88, 55.88), (322.58, 55.88)); sh.label('LCD_RES', (322.58, 55.88), (1, 0))
    sh.text('Power-on reset (τ = 1 ms);\nfirmware adds a SWRESET.', (294.64, 76.2), size=1.27)
    # backlight switch (high side)
    qp = place_part(sh, 'Q_P_SOT23', 'Q101', 233.68, 58.42, mirror='x', ref_at=(5.08, -1.27, 'left'), val_at=(5.08, 1.27, 'left'))
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    sh.wire((sx, sy), (sx, sy - 5.08)); sh.power('+3V3', (sx, sy - 5.08)); sh.assign(qp, 'S', '+3V3')
    yb = dy + 5.08
    sh.wire((dx, dy), (dx, yb)); sh.assign(qp, 'D', 'BL_OUT')
    sh.wire((dx, yb), (dx + 7.62, yb)); sh.label('BL_OUT', (dx + 7.62, yb), (1, 0))
    vpart_between(sh, 'R_1k', 'R109', dx, yb, ('net', 'BL_OUT'), 'GND')
    rpu = vpart_between(sh, 'R_10k', 'R102', gx - 10.16, gy - 10.16, '+3V3', None)
    sh.connect('BL_G', (rpu, '2'), (gx - 10.16, gy), (qp, 'G'))
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    rg = place_part(sh, 'R_100', 'R103', ngx - 17.78, ngy, rot=90)
    sh.connect('BL_GN', (rg, '2'), (qn, 'G'))
    vpart_between(sh, 'R_100k', 'R104', ngx - 7.62, ngy, ('net', 'BL_GN'), 'GND')
    (r1x, r1y), _ = rg.pin('1'); sh.assign(rg, '1', 'LCD_BL')
    sh.wire((r1x, r1y), (r1x - 7.62, r1y)); sh.label('LCD_BL', (r1x - 7.62, r1y), (-1, 0))
    sh.text('LCD_BL = 1 → Q102 on → Q101 on → BLK = 3.3 V. R109 holds BLK at 0 V when off\n(modules with internal BLK pull-up). Suits logic BLK or a direct LED. PWM ≤ 5 kHz.', (134.62, 99.06), size=1.27)

    # ------------------------------------------------------------------ ToF
    t = place_part(sh, 'U_VL53L1X', 'U101', 190.5, 182.88, ref_at=(10.16, 6.35, 'left'), val_at=(10.16, 8.89, 'left'))
    sh.pin_label(t, 'SDA', 'I2C_SDA', length=15.24)
    sh.pin_label(t, 'SCL', 'I2C_SCL', length=15.24)
    sh.pin_label(t, 'GPIO1', 'TOF_INT', length=15.24)
    sh.pin_label(t, 'XSHUT', 'TOF_XSHUT', length=15.24)
    sh.assign(t, '8', '__NC__U101.8')
    (ax, ay), _ = t.pin('AVDD'); (vx, vy), _ = t.pin('AVDDVCSEL')
    sh.assign(t, 'AVDD', '+3V3'); sh.assign(t, 'AVDDVCSEL', '+3V3')
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        r = vpart_between(sh, 'R_10k', ref, x, 208.28, '+3V3', None)
        (bx, by), _ = r.pin('2'); sh.assign(r, '2', net)
        sh.wire((bx, by), (bx, by + 5.08)); sh.label(net, (bx, by + 5.08), (0, 1))
    sh.text('Optical window facing forward (vertical board).\nXSHUT pulled up: ToF active even if the expander\nis not configured yet. GPIO1 is open-drain.', (134.62, 236.22), size=1.27)

    # ------------------------------------------------------------------ camera (mechanical)
    for i, ref in enumerate(('H103', 'H104', 'H105', 'H106')):
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
    # ------------------------------------------------------------------ touch
    q = place_part(sh, 'U_QT1010', 'U103', 322.58, 220.98, ref_at=(-7.62, -7.62, 'right'), val_at=(-7.62, 7.62, 'right'))
    (ox, oy), _ = q.pin('OUT'); sh.assign(q, 'OUT', 'TOUCH')
    sh.wire((ox, oy), (ox - 17.78, oy)); sh.label('TOUCH', (ox - 17.78, oy), (-1, 0))
    (syx, syy), _ = q.pin('SYNC'); sh.assign(q, 'SYNC', '+3V3')
    sh.wire((syx, syy), (syx - 5.08, syy)); sh.wire((syx - 5.08, syy), (syx - 5.08, syy - 10.16)); sh.power('+3V3', (syx - 5.08, syy - 10.16))
    (vx, vy), _ = q.pin('VDD'); sh.assign(q, 'VDD', '+3V3')
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
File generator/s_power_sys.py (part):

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    sh.wire((bpx + 5.08, yb), (flx, yb)); sh.assign(f, fl, 'BAT+'); sh.assign(f, fr, 'VBAT')
    xv = 106.68
    sh.wire((frx, yb), (xv, yb)); sh.power('VBAT', (73.66, yb))
    sh.wire((bmx, bmy), (bmx + 12.7, bmy)); sh.label('BAT_BM', (bmx + 12.7, bmy), (1, 0)); sh.assign(j, '2', 'BAT_BM')
    sh.wire((bnx, bny), (bnx + 12.7, bny)); sh.label('BAT-', (bnx + 12.7, bny), (1, 0)); sh.assign(j, '1', 'BAT-')
    sh.text('2S2P Li-ion pack (JST VH, 10 A):\n1 = B−, 2 = midpoint, 3 = B+', (25.4, 73.66), size=1.27, italic=True)

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    (a2x, a2y), _ = r2.pin('1'); (b2x, b2y), _ = r2.pin('2')
    l2, rr2 = ('1', '2') if a2x < b2x else ('2', '1')
    (l2x, l2y), _ = r2.pin(l2); (rr2x, rr2y), _ = r2.pin(rr2)
    sh.wire((l2x, l2y), (l2x - 5.08, l2y)); sh.label('BAT_BM', (l2x - 5.08, l2y), (-1, 0)); sh.assign(r2, l2, 'BAT_BM')
    sh.wire((rr2x, rr2y), (vcx, vcy)); sh.assign(r2, rr2, 'PROT_VC'); sh.assign(u, 'VC', 'PROT_VC')
    xc2 = vcx - 2.54
    sh.wire((xc2, vcy), (xc2, vcy + 5.08))
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        sh.text(title, (210.82, y0 - 27.94), size=1.524, bold=True)
    ux = 259.08
    u = place_part(sh, 'U_TPS62933', U, ux, y0, ref_at=(-5.08, -12.065, 'left'), val_at=(-2.54, 15.875, 'right'))
    (vx, vy), _ = u.pin('VIN'); sh.assign(u, 'VIN', 'VSYS')
    yr = y0 - 20.32; xr = vx - 7.62
    sh.wire((vx, vy), (xr, vy)); sh.wire((xr, vy), (xr, yr)); sh.wire((xr, yr), (231.14, yr))
    sh.power('VSYS', (xr, yr))
    cap_rail(sh, 'VSYS', 218.44, yr, [(CIN1, 'C_22u_25V'), (CIN2, 'C_100n')], dx=12.7)
    sh.pin_label(u, 'EN', 'PWR_EN', length=12.7)
    (sx, sy), _ = u.pin('SS'); sh.assign(u, 'SS', f'{U}_SS')
    sh.wire((sx, sy), (sx - 15.24, sy))
    vpart_between(sh, 'C_33n', CSS, sx - 15.24, sy, ('net', f'{U}_SS'), 'GND')
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    ux, uy = 279.4, 116.84
    u = place_part(sh, 'U_TPS566238', 'U302', ux, uy, ref_at=(-7.62, -12.7, 'left'), val_at=(-7.62, 13.97, 'left'))
    # VIN from VSYS with the input capacitors
    (vx, vy), _ = u.pin('VIN'); sh.assign(u, 'VIN', 'VSYS')
    yr, xr = 91.44, vx - 7.62
    sh.wire((vx, vy), (xr, vy)); sh.wire((xr, vy), (xr, yr)); sh.power('VSYS', (xr, yr))
    sh.wire((256.54, yr), (xr, yr))
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    vpart_between(sh, 'C_1u', 'C305', cx - 5.08, cy, ('net', 'U302_VCC'), 'GND')
    sh.pin_power(u, 'PGND', 'GND', length=2.54)
    # EN: pull-up to +3V3 (alive only while the 3.3 V buck runs) and Q303 driven by the ESP32
    (ex, ey), _ = u.pin('EN'); sh.assign(u, 'EN', 'PI_EN')
    xn = 236.22
    sh.wire((xn, ey), (ex, ey)); sh.label('PI_EN', (251.46, ey), (0, -1))
    rpu = vpart_between(sh, 'R_100k', 'R310', xn, ey - 10.16, '+3V3', None)
    (rpx, rpy), _ = rpu.pin('2'); sh.assign(rpu, '2', 'PI_EN'); sh.wire((rpx, rpy), (rpx, ey))
    vpart_between(sh, 'C_1n', 'C312', xn + 10.16, ey, ('net', 'PI_EN'), 'GND')
    q = place_part(sh, 'Q_2N7002', 'Q303', xn - 2.54, ey + 10.16)
    (qdx, qdy), _ = q.pin('D'); (qgx, qgy), _ = q.pin('G')
    sh.wire((qdx, qdy), (qdx, ey)); sh.assign(q, 'D', 'PI_EN')
    sh.pin_power(q, 'S', 'GND', length=2.54)
    sh.wire((qgx, qgy), (qgx - 10.16, qgy)); sh.assign(q, 'G', 'PI_PWR_OFF')
    sh.hlabel('PI_PWR_OFF', (qgx - 10.16, qgy), (-1, 0), 'input')
    vpart_between(sh, 'R_100k', 'R312', qgx - 5.08, qgy, ('net', 'PI_PWR_OFF'), 'GND')
    # BST and SW
    (bx, by), _ = u.pin('BST'); sh.assign(u, 'BST', 'U302_BST')
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    rt = vpart_between(sh, 'R_182k', 'R301', xf, loy, ('net', '+5V'), None)
    rbt = vpart_between(sh, 'R_24k', 'R302', xf, loy + 10.16, None, 'GND')
    sh.connect('U302_FB', (rt, '2'), (rbt, '1'))
    sh.wire((xf, loy + 8.89), (xf - 5.08, loy + 8.89)); sh.label('U302_FB', (xf - 5.08, loy + 8.89), (-1, 0))
    sh.wire((xf, loy), (xf + 7.62, loy))
    cff = vpart_between(sh, 'C_33p', 'C311', xf + 7.62, loy, ('net', '+5V'), None)
    (c3x, c3y), _ = cff.pin('2'); sh.assign(cff, '2', 'U302_FB')
    sh.wire((c3x, c3y), (c3x, loy + 8.89)); sh.wire((c3x, loy + 8.89), (xf, loy + 8.89))
    (fx, fy), _ = u.pin('FB'); sh.assign(u, 'FB', 'U302_FB')
    sh.wire((fx, fy), (fx + 7.62, fy)); sh.label('U302_FB', (fx + 7.62, fy), (1, 0))
    # PG → expander, pull-up to +3V3
    (gx, gy), _ = u.pin('PG'); sh.assign(u, 'PG', 'PI_5V_PG')
    yp = gy + 10.16
    sh.wire((gx, gy), (gx + 5.08, gy)); sh.wire((gx + 5.08, gy), (gx + 5.08, yp)); sh.wire((gx + 5.08, yp), (gx + 25.4, yp))
    rpg = vpart_between(sh, 'R_10k', 'R313', gx + 15.24, yp - 7.62, '+3V3', ('net', 'PI_5V_PG'))
    sh.hlabel('PI_5V_PG', (gx + 25.4, yp), (1, 0), 'output')
    sh.text('Vout = 0.6 V × (1 + 182k/24.0k) = 5.15 V (Pi 5 input 5.0–5.25 V). D-CAP3 at 600 kHz; 98 % max duty (frequency\n'
            'foldback): regulates 5.15 V at 5 A down to ≈ 5.5 V in. L301 2.2 µH (Isat 11 A); valley limit ≥ 6.1 A. Cout 3×47 µF\n'
            '(≈ 75 µF effective at 5 V, limit 220 µF incl. C701). EN: pulled to +3V3 (off with the 3.3 V rail = power switch);\n'
            'PI_PWR_OFF high (ESP32 GPIO1, held in deep sleep) turns the Pi rail off after the shutdown handshake. PG → U402 P12.',
            (210.82, 152.4), size=1.27)

def build(sh):
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    sw = place_part(sh, 'SW_SLIDE', 'SW301', 266.7, y, ref_at=(-2.54, -6.35, 'left'), val_at=(-2.54, 6.35, 'left'))
    (sbx, sby), _ = sw.pin('B'); (sax, say), _ = sw.pin('A'); (scx, scy), _ = sw.pin('C')
    sh.wire((xn, y), (sbx, sby)); sh.assign(sw, 'B', 'PWR_EN')
    sh.label('PWR_EN', (251.46, y), (1, 0))
    sh.wire((sax, say), (sax + 5.08, say)); sh.wire((sax + 5.08, say), (sax + 5.08, say + 7.62))
    sh.power('GND', (sax + 5.08, say + 7.62)); sh.assign(sw, 'A', 'GND')
    sh.pin_nc(sw, 'C')
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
